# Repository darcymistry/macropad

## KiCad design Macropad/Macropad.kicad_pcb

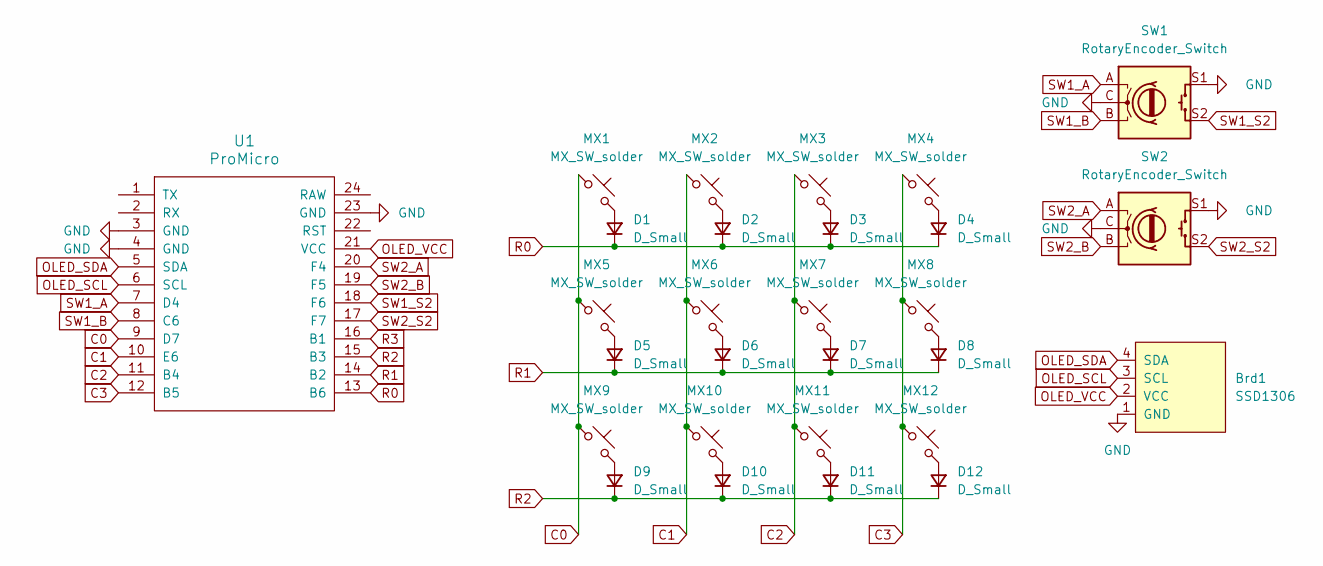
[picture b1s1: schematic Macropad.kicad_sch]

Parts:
Brd1: SSD1306; 128x64OLED
D1, D2, D3, D4, D5, D6, D7, D8, D9, D10, D11, D12: D_Small; D_SOD-123
MX1, MX2, MX3, MX4, MX5, MX6, MX7, MX8, MX9, MX10, MX11, MX12: MX_SW_solder; SW_MX_1u
SW1, SW2: RotaryEncoder_Switch; RotaryEncoder_Alps_EC11E-Switch_Vertical_H20mm_CircularMoun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
U1: ProMicro; ArduinoProMicro

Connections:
C0: MX1.1, MX5.1, MX9.1, U1.9 (D7)
C1: MX2.1, MX6.1, MX10.1, U1.10 (E6)
C2: MX3.1, MX7.1, MX11.1, U1.11 (B4)
C3: MX4.1, MX8.1, MX12.1, U1.12 (B5)
GND: Brd1.1 (GND), SW1.C, SW1.S1, SW2.C, SW2.S1, U1.3 (GND), U1.4 (GND), U1.23 (GND)
unnamed: D1.2 (A), MX1.2
unnamed: D2.2 (A), MX2.2
unnamed: D3.2 (A), MX3.2
unnamed: D4.2 (A), MX4.2
unnamed: D5.2 (A), MX5.2
unnamed: D6.2 (A), MX6.2
unnamed: D7.2 (A), MX7.2
unnamed: D8.2 (A), MX8.2
unnamed: D9.2 (A), MX9.2
unnamed: D10.2 (A), MX10.2
unnamed: D11.2 (A), MX11.2
unnamed: D12.2 (A), MX12.2
OLED_SCL: Brd1.3 (SCL), U1.6 (SCL)
OLED_SDA: Brd1.4 (SDA), U1.5 (SDA)
OLED_VCC: Brd1.2 (VCC), U1.21 (VCC)
R0: D1.1 (K), D2.1 (K), D3.1 (K), D4.1 (K), U1.13 (B6)
R1: D5.1 (K), D6.1 (K), D7.1 (K), D8.1 (K), U1.14 (B2)
R2: D9.1 (K), D10.1 (K), D11.1 (K), D12.1 (K), U1.15 (B3)
R3: U1.16 (B1)
SW1_A: SW1.A, U1.7 (D4)
SW1_B: SW1.B, U1.8 (C6)
SW1_S2: SW1.S2, U1.18 (F6)
SW2_A: SW2.A, U1.20 (F4)
SW2_B: SW2.B, U1.19 (F5)
SW2_S2: SW2.S2, U1.17 (F7)

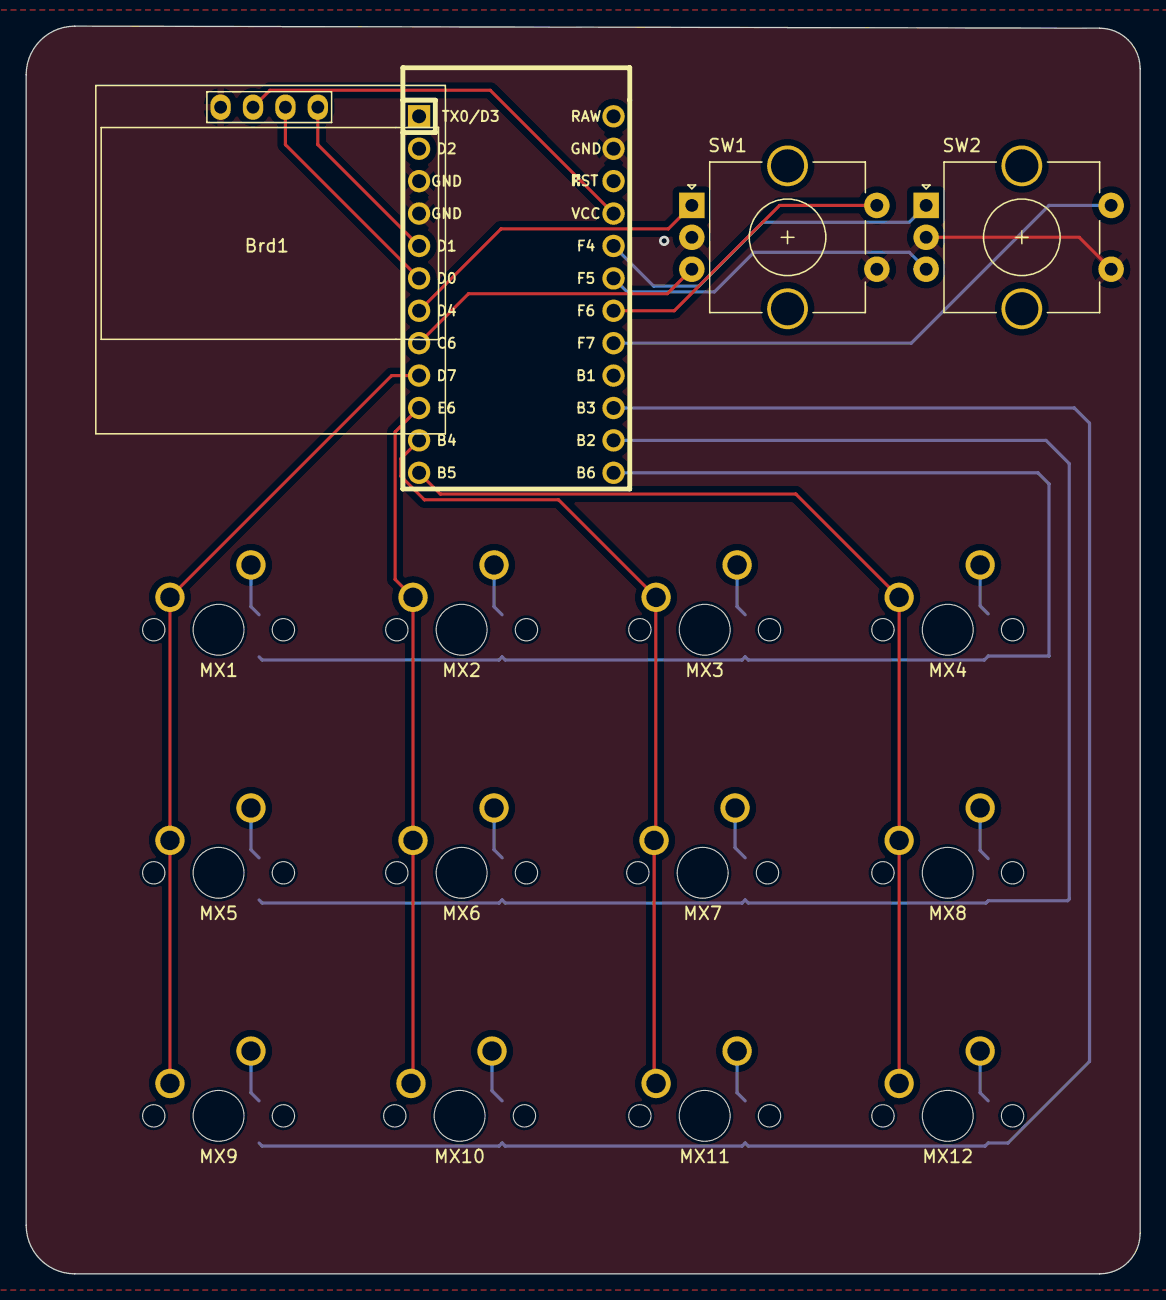
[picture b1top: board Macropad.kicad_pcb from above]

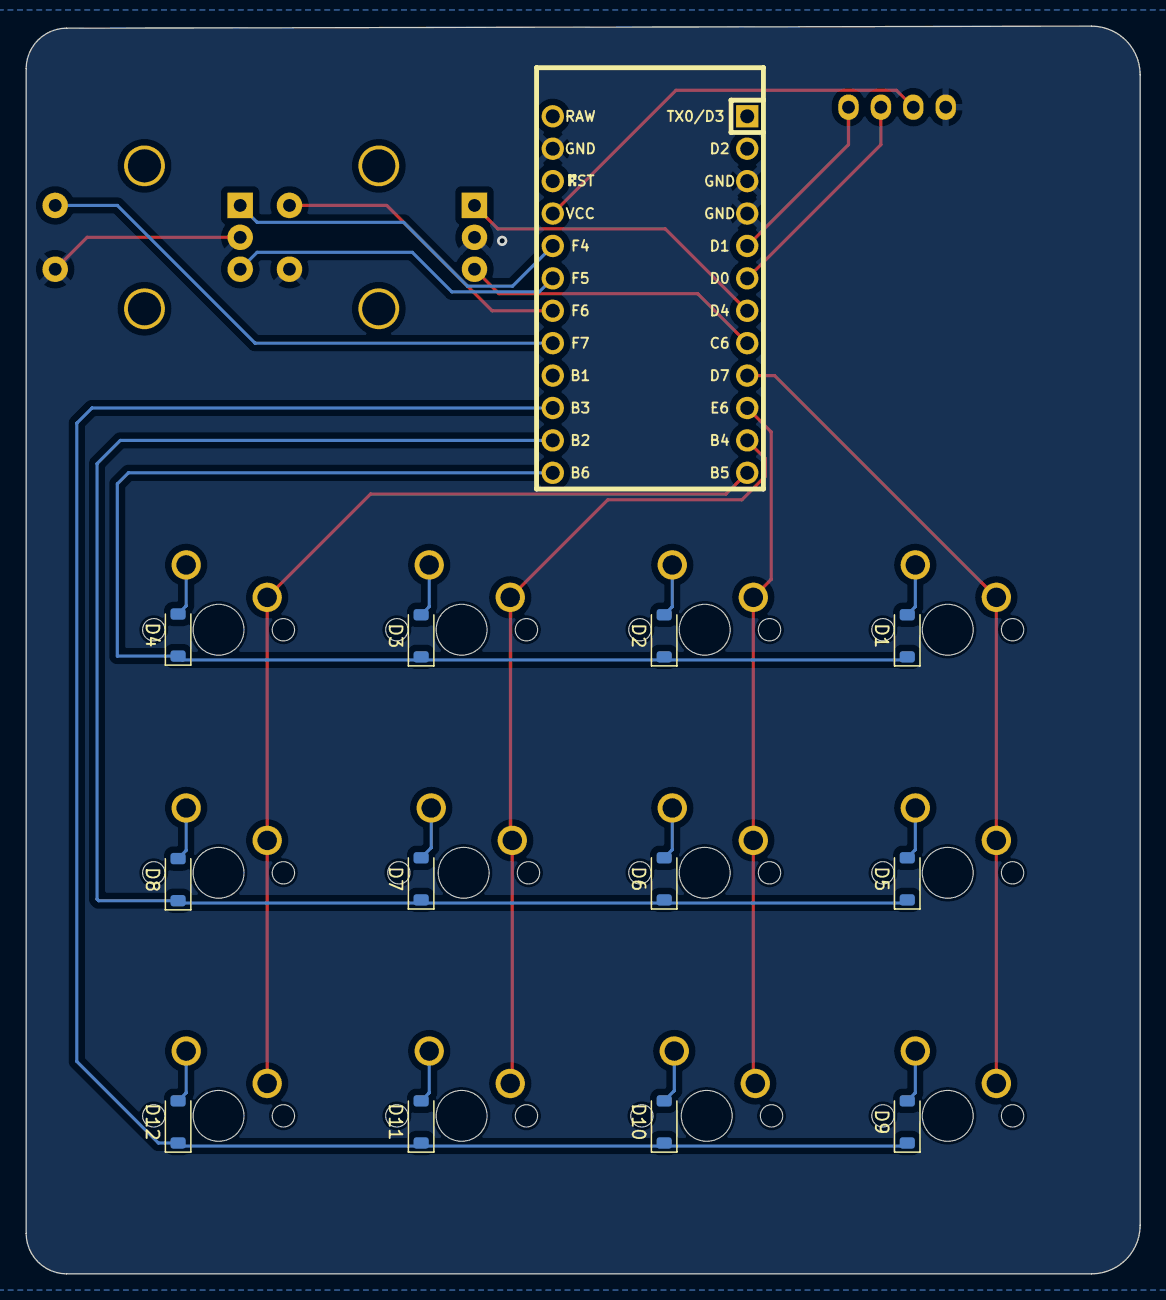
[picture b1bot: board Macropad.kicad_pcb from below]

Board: 2 copper layers, 87.3 x 97.8 mm, 28 parts (12 on the bottom side), 29 nets.
